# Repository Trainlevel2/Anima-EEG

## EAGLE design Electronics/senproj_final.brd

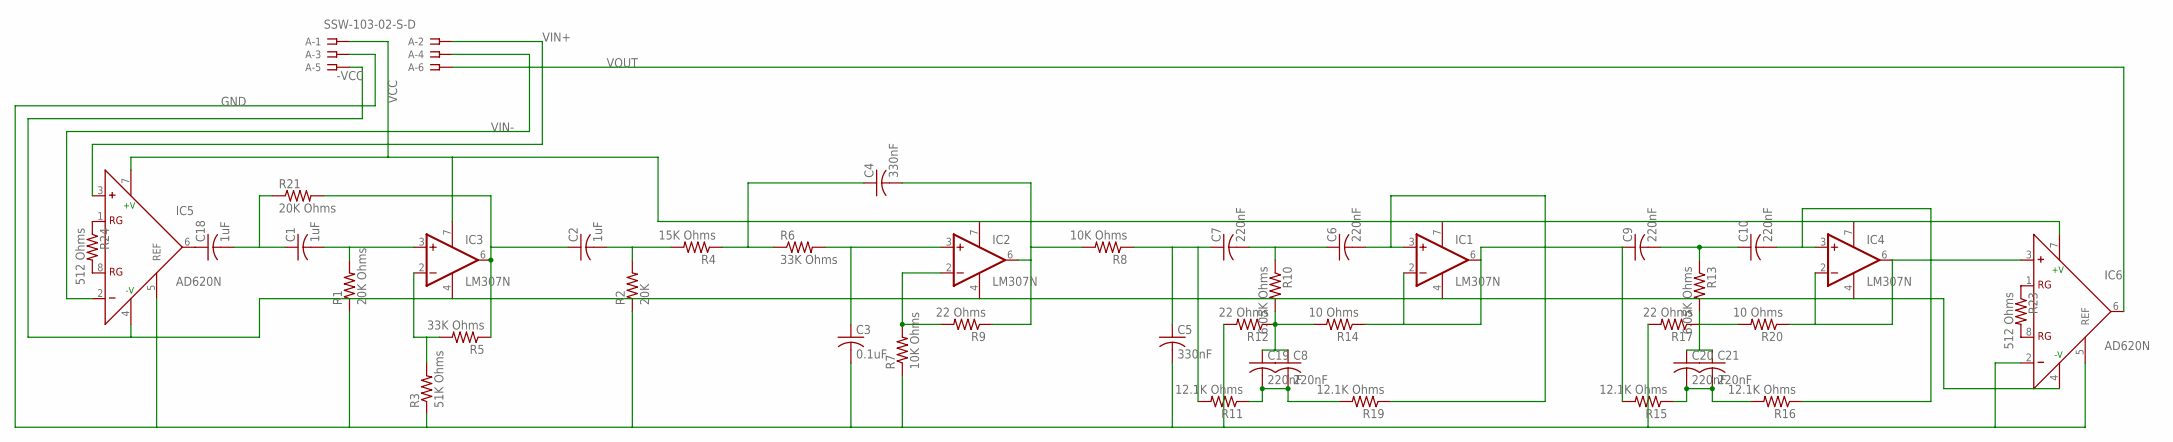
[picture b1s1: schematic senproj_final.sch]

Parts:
A: SSW-103-02-S-D
C1, C2, C18: 1uF; C150-054X183
C3: 0.1uF; C075-032X103
C4, C5: 330nF; C102-043X133
C6, C7, C8, C9, C10, C19, C20, C21: 220nF; C050-024X044
IC1, IC2, IC3, IC4: LM307N; DIL08
IC5, IC6: AD620N; DIL08
R1, R21: 20K Ohms; 0204/7
R2: 20K; 0204/7
R3: 51K Ohms; 0204/7
R4: 15K Ohms; 0204/7
R5, R6: 33K Ohms; 0204/7
R7, R8: 10K Ohms; 0204/7
R9, R12, R17: 22 Ohms; 0204/7
R10, R13: 6.05K Ohms; 0204/7
R11, R15, R16, R19: 12.1K Ohms; 0204/7
R14, R20: 10 Ohms; 0204/7
R23, R24: 512 Ohms; 0204/7

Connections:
-VCC: A.5, IC1.4 (V-), IC2.4 (V-), IC3.4 (V-), IC4.4 (V-), IC5.4 (-V), IC6.4 (-V)
GND: A.3, C3.2, C5.2, IC5.5 (REF), IC6.2 (-), IC6.5 (REF), R1.1, R2.1, R3.1, R7.1, R12.2, R17.2
unnamed: C1.1, C18.2, R21.1
unnamed: C1.2, IC3.3 (+IN), R1.2
unnamed: C4.1, R4.1, R6.1
unnamed: IC3.2 (-IN), R3.2, R5.2
unnamed: C18.1, IC5.6 (OUT)
unnamed: C2.1, IC3.6 (OUT), R5.1, R21.2
unnamed: C2.2, R2.2, R4.2
unnamed: IC2.2 (-IN), R7.2, R9.2
unnamed: C3.1, IC2.3 (+IN), R6.2
unnamed: C4.2, IC2.6 (OUT), R8.2, R9.1
unnamed: C5.1, C7.1, R8.1, R11.2
unnamed: C8.1, C19.1, R10.2, R12.1, R14.2
unnamed: C6.1, C7.2, R10.1
unnamed: C8.2, C19.2, R11.1, R19.2
unnamed: C6.2, IC1.3 (+IN), R19.1
unnamed: C9.1, IC1.2 (-IN), IC1.6 (OUT), R14.1, R15.2
unnamed: C20.1, C21.1, R13.2, R17.1, R20.2
unnamed: C9.2, C10.1, R13.1
unnamed: C20.2, C21.2, R15.1, R16.2
unnamed: C10.2, IC4.3 (+IN), R16.1
unnamed: IC4.2 (-IN), IC4.6 (OUT), IC6.3 (+), R20.1
unnamed: IC5.8 (RG), R24.2
unnamed: IC5.1 (RG), R24.1
unnamed: IC6.8 (RG), R23.2
unnamed: IC6.1 (RG), R23.1
VCC: A.1, IC1.7 (V+), IC2.7 (V+), IC3.7 (V+), IC4.7 (V+), IC5.7 (+V), IC6.7 (+V)
VIN+: A.2, IC5.3 (+)
VIN-: A.4, IC5.2 (-)
VOUT: A.6, IC6.6 (OUT)

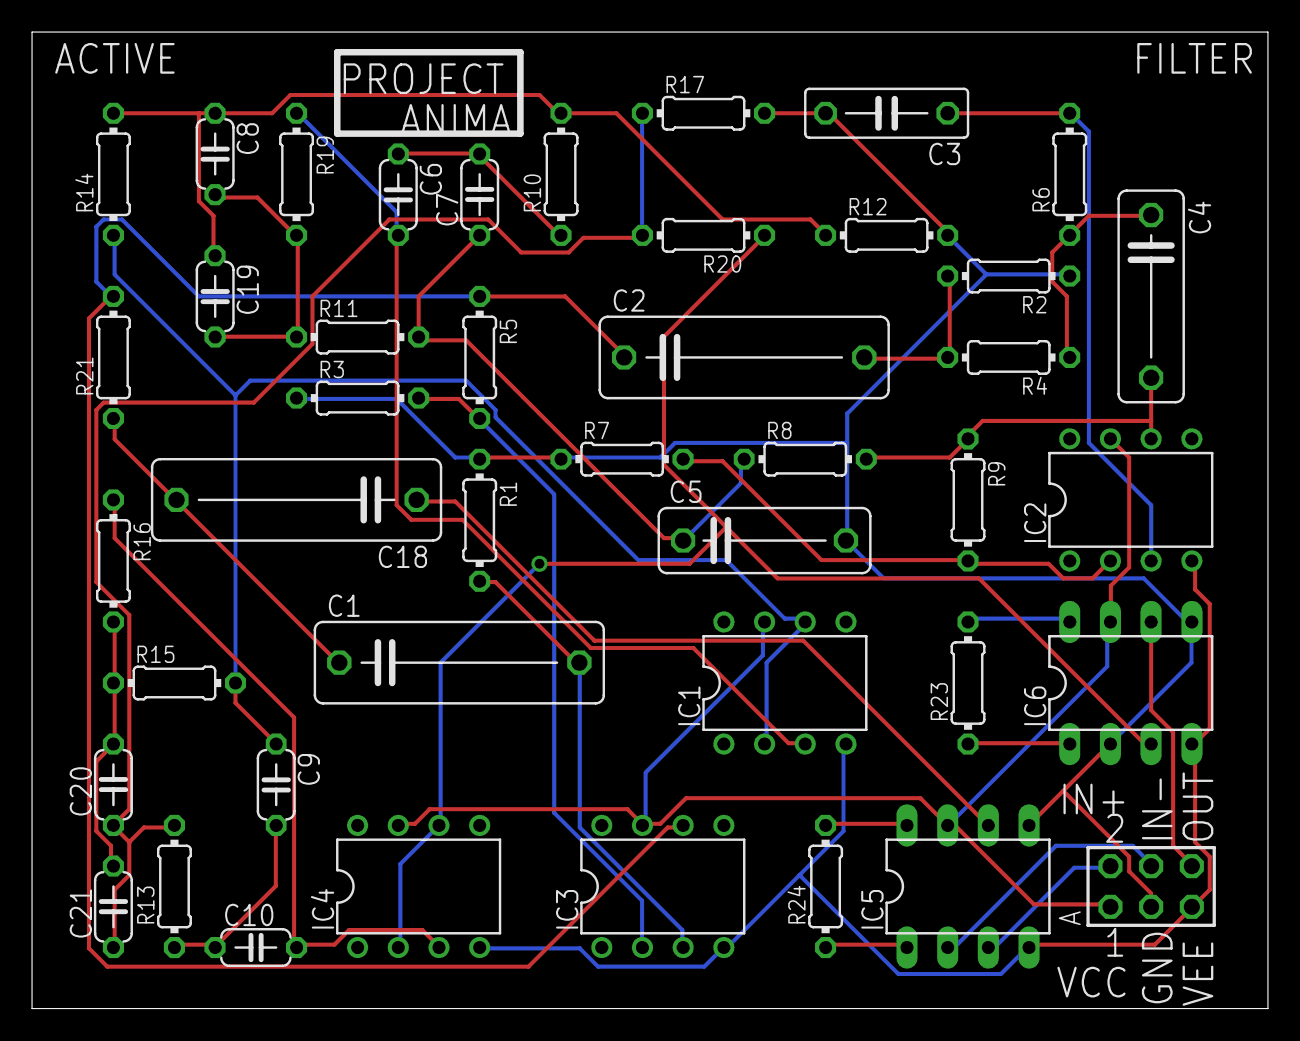
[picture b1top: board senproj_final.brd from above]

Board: 2 copper layers, 77.1 x 60.9 mm, 43 parts (0 on the bottom side), 31 nets.

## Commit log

2017-01-31 :lollipop: Added .gitattributes
2017-01-31 Notch Filter Designs and Such
2017-01-31 Create README.md
    just a temp one for now tho
2017-02-02 Added another notch filter lol
2017-02-04 Added Experimental Frequency Response for Active Filter
    Also some directory changes
2017-02-05 Working active sensor
2017-02-09 More experimental results
2017-03-02 My Results
    Check it, it works okay I think, but perhaps not as great as yours
2017-03-06 Python-MATLAB Socket Connection Examples
    Made a Python file that opens a socket that the accompanying MATLAB files, testserverpython.m and pymat.m, can access and send data (a string) through.
2017-03-06 Added ActiveElectrode.asc
    ActiveElectrode.asc has the current electrode design, except for
    instrumentation amplifiers...
    Also changed directory structure a bit to simplify and clarify
2017-03-20 Started learning Tensorflow
    Put some tensorflow examples up for fun and stuff
2017-03-25 Use arduino for signal acquisition
2017-03-25 removed old active sensor schematic
2017-03-25 MATLAB folder became software folder to include python and arduino files too
2017-03-25 Arduino signal acquisition code
2017-03-25 Wrog place
2017-04-02 Change to active electrode schematic
    2.2k -> 22k as per PCB errors
2017-04-02 Added comments for clarity, left commented code
2017-04-02 Added Eagle Files for PCBs
2017-04-03 pcb characterization
    they're all pretty similar tbh
2017-04-03 more data
2017-04-03 Added movemouse fn and example
    The added function takes in 6 parameters: Robot object (for mouse movement), initial position x, initial position y, displacement x, displacement y, speed (1 is a good amount, 3 is great for testing)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
2017-04-03 Keep calm and classify on
    Needs some work, but can classify reasonably well if there is a key threshold.
2017-04-03 Arrays in MATLAB start at 1...
2017-04-03 Code for three active sensors
    (for 1D mouse control)
2017-04-03 Code for 3 active sensors
2017-04-04 Integrated All Software Components (WIP)
    The two+ input arrays need to be connected to the data received from the classifier. Adding a simple counter that adds to an array of frequencies/amplitudes and then using that should work, but I nee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
2017-04-04 data
2017-04-04 add labels for plots
2017-04-04 Changed to adapt to Arduino code changes
    I will continue to update this, but I still need someone to take a look at it
2017-04-04 more data, ratios graphed now
2017-04-04 presentation today
    here's code right before it
2017-04-10 neural network works for test data...
    works for cancer data
    update to get it working with eeg
2017-04-17 Fixed code and save training data in .mat file.
2017-04-19 updated matlab and data
2017-04-19 updated EEGTrain for different test times and loading previous data for multiple training sessions
2017-04-19 testing nn...
2017-04-21 merged data works too now
    lolol
2017-04-23 more test results
2017-04-23 moar data
2017-04-23 dc values are also important
2017-04-25 raw training data
2017-05-02 added EEGTest.m, for using the trained neural network
2017-05-02 Added node optimizer.
2017-05-02 Fixed node optimizer
2017-05-02 it works!!! (with a nn now ayy)
2017-05-04 graphs lol
2017-05-09 ayy final paper done! senior projects technically complete
    may still work for end of year show tho lol
2017-05-16 reorganize old files into archive folders
